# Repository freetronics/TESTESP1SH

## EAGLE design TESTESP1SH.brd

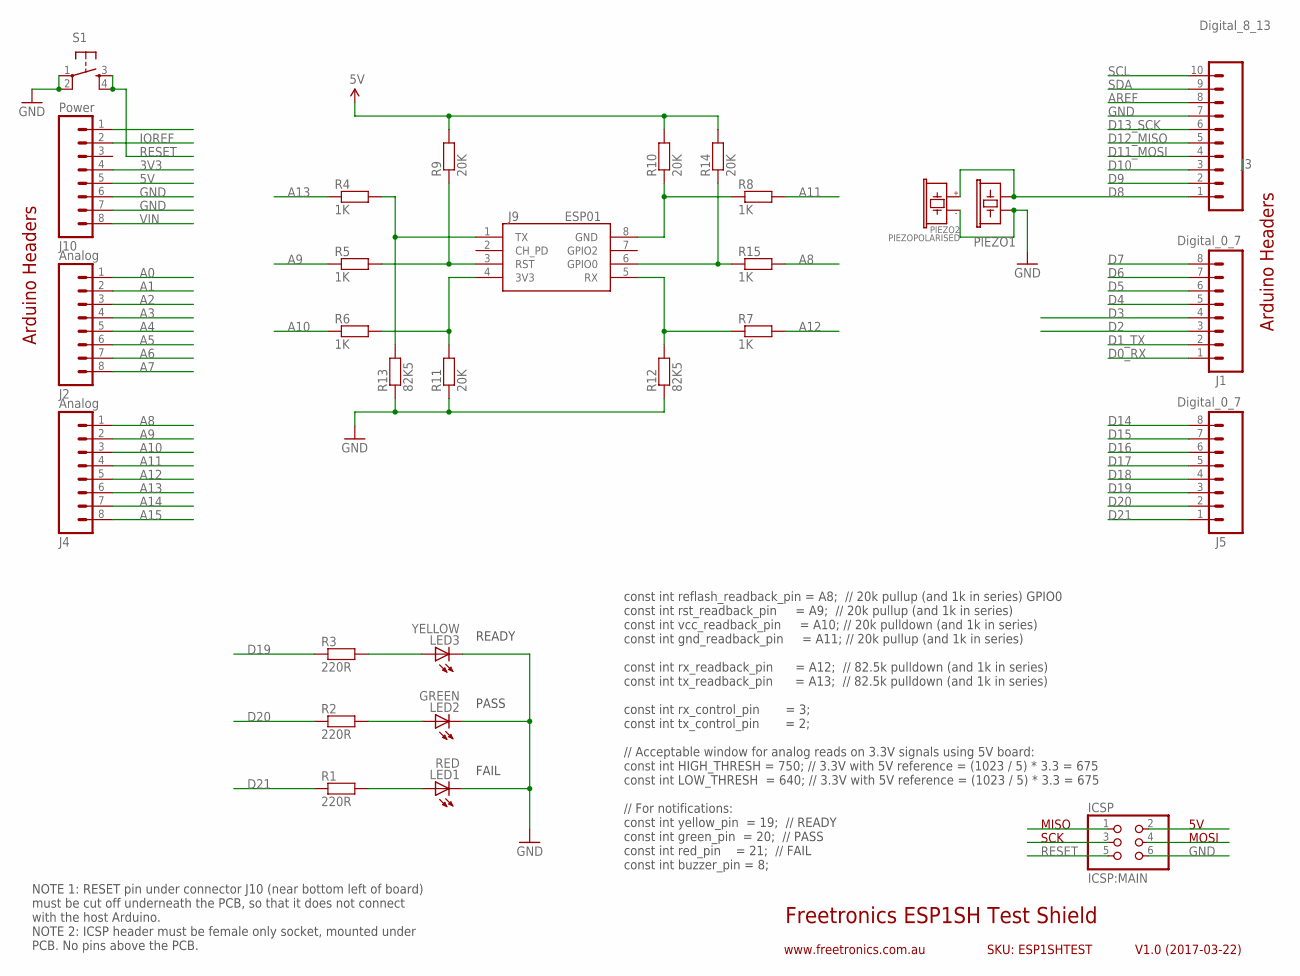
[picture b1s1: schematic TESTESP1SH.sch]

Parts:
ICSP: ICSP:MAIN; 2X03
J1, J5: Digital_0_7; 1X08
J2, J4: Analog; 1X08
J3: Digital_8_13; 1X10
J9: ESP01
J10: Power; 1X08
LED1: RED; LED-0603
LED2: GREEN; LED-0603
LED3: YELLOW; LED-0603
PIEZO1: BUZZERSMD12X12; BUZZER-12X12-SMT
PIEZO2: PIEZOPOLARISED; PIEZO12MMWIDEPOLARISED
R1, R2, R3: 220R; 0603
R4, R5, R6, R7, R8, R15: 1K; 0603
R9, R10, R11, R14: 20K; 0603
R12, R13: 82K5; 0603
S1: TAC_SWITCHPTH; TACTILE-PTH

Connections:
3V3: J10.4
5V: J10.5, R9.2, R10.2, R14.2
A0: J2.1
A1: J2.2
A2: J2.3
A3: J2.4
A4: J2.5
A5: J2.6
A6: J2.7
A7: J2.8
A8: J4.1, R15.2
A9: J4.2, R5.1
A10: J4.3, R6.1
A11: J4.4, R8.2
A12: J4.5, R7.2
A13: J4.6, R4.1
A14: J4.7
A15: J4.8
AREF: J3.8
D0_RX: J1.1
D1_TX: J1.2
D2: J1.3
D3: J1.4
D4: J1.5
D5: J1.6
D6: J1.7
D7: J1.8
D8: J3.1, PIEZO1.1, PIEZO2.1 (+)
D9: J3.2
D10: J3.3
D11_MOSI: J3.4
D12_MISO: J3.5
D13_SCK: J3.6
D14: J5.8
D15: J5.7
D16: J5.6
D17: J5.5
D18: J5.4
D19: J5.3, R3.1
D20: J5.2, R2.1
D21: J5.1, R1.1
GND: ICSP.6, J3.7, J10.6, J10.7, LED1.C, LED2.C, LED3.C, PIEZO1.2, PIEZO2.2 (-), R11.1, R12.1, R13.1, S1.1, S1.2
IOREF: J10.2
unnamed: LED3.A, R3.2
unnamed: LED2.A, R2.2
unnamed: LED1.A, R1.2
unnamed: J9.3 (RST), R5.2, R9.1
unnamed: J9.8 (GND), R8.1, R10.1
unnamed: J9.4 (3V3), R6.2, R11.2
unnamed: J9.5 (RX), R7.1, R12.2
unnamed: J9.1 (TX), R4.2, R13.2
unnamed: J9.6 (GPIO0), R14.1, R15.1
RESET: ICSP.5, S1.3, S1.4
SCL: J3.10
SDA: J3.9
VIN: J10.8

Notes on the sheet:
Freetronics ESP1SH Test Shield
V1.0 (2017-03-22)
www.freetronics.com.au
SKU: ESP1SHTEST
Arduino Headers
MISO
SCK
MOSI
READY
PASS
FAIL
NOTE 1: RESET pin under connector J10 (near bottom left of board) must be cut off underneath the PCB, so that it does not connect with the host Arduino. NOTE 2: ICSP header must be female only socket, mounted under PCB. No pins above the PCB.
const int reflash_readback_pin = A8; // 20k pullup (and 1k in series) GPIO0 const int rst_readback_pin = A9; // 20k pullup (and 1k in series) const int vcc_readback_pin = A10; // 20k pulldown (and 1k in series) const int gnd_readback_pin = A11; // 20k pullup (and 1k in series) const int rx_readback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

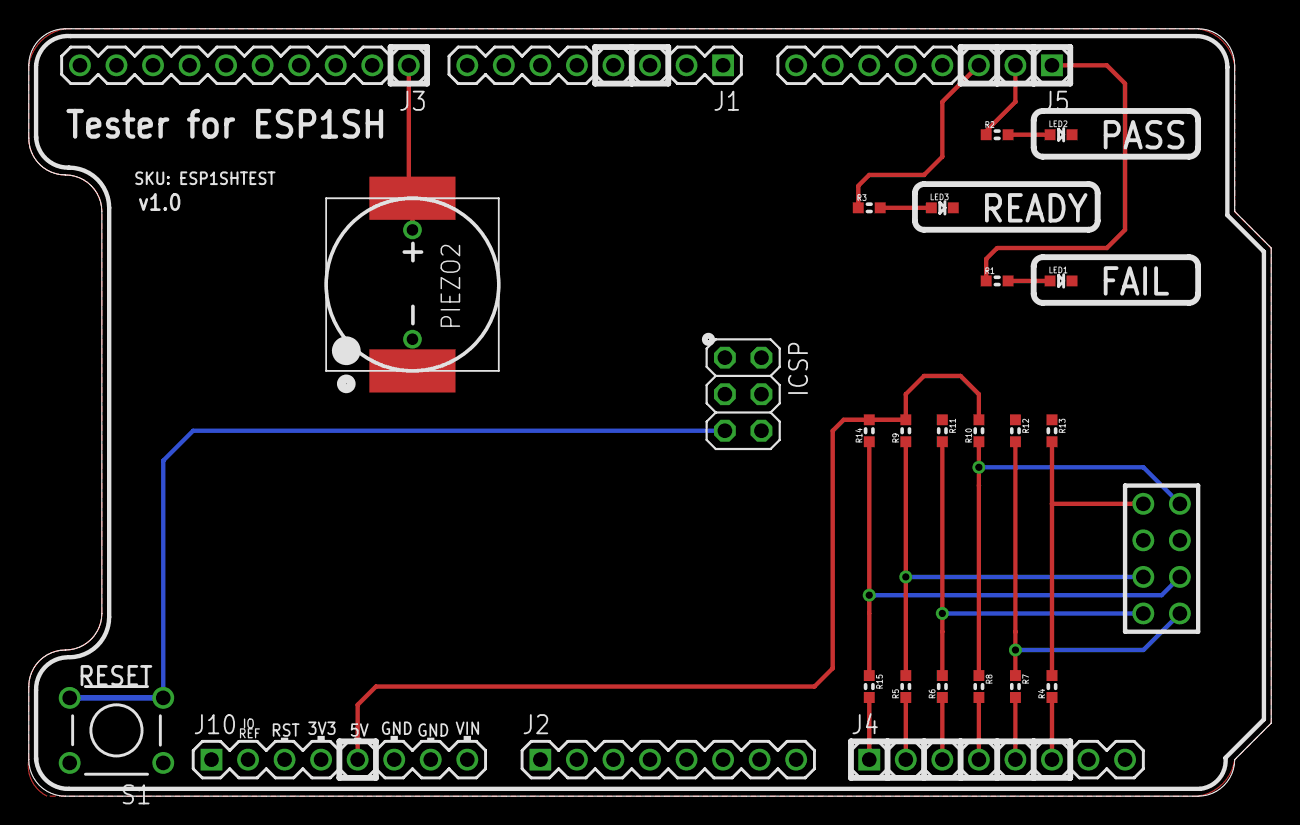
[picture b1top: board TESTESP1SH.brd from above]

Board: 2 copper layers, 86.4 x 53.3 mm, 29 parts (0 on the bottom side), 22 nets.

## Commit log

2017-03-22 Initial project import
2019-04-24 Changes for v2.0 release

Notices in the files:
TESTESP1SH.brd:
(C) 2017
